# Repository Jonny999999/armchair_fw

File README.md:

# Overview
This repository contains the firmware for a custom-built automated electric armchair.  
Detailed project information and documentation is available on the website:
- ~~V1: [Electric Armchair V1](https://pfusch.zone/electric-armchair)~~
- V2: [Electric Armchair V2](https://pfusch.zone/electric-armchair-v2)

**Note:** Only the esp-project in the [board_single/](board_single) folder and the custom libraries in [common/](common) are used.  
The two-board V2.1 approach (`board_control`/`board_motorctl`) was dropped and its code removed; see tag `V2.2_new-driver` or earlier if that history is ever needed again.

<br>
*Photo of the built frame that carries the armchair*

<br>

## Current Features
- **Control Modes:**
  - **Joystick:** Control movement via hardware joystick mounted on the right armrest
  - **HTTP:** Control movement via virtual joystick on a web interface
  - **Massage:** Armchair shaking depending on stick position
  - **Adjust:** Control leg and backrest position via joystick
  - **Auto:** Execute stored driving commands sequentially
- **Advanced Motor Control:**
  - Deceleration limit
  - Acceleration limit
  - Current limit
  - Braking
  - Compatible with different motor drivers:
    - 3 pins: A, B, PWM - e.g. various common H-Bridges
    - 1 pin: UART/RS232 - e.g. Sabertooth
- **Input/Sensors:**
  - **Speed Measurement:** Measures speed and direction of each tire individually using custom built encoders
  - **Current Measurement:** Monitors current of each motor
  - **Battery Voltage:** Measures battery voltage and calculates percentage according to discharge curve
  - **Analog Joystick:** 
    - Evaluate two analog signals to get coordinates, radius and angle
    - Calibration wizard/sequence
    - Calibration stored persistently in nvs
- **Fan Control:** Cooling fan for motor driver are activated when needed only
- **Buzzer:** Provides acoustic feedback when switching modes or interacting with menu
- **OLED-Display + Rotary-encoder:**
  - Various status screens showing battery status, speed, RPM, motor current, mode, power, duty cycle, stick data
  - Menu for setting various options using encoder
  - Changed settings are stored persistently in NVS flash
  - Menu for selecting the control mode
- **UART Communication between 2 Boards (V2.1)**
- **Electric Chair Adjustment:** Control 4 Relays powering motors that adjust the chair rest positions
- **Wi-Fi:**
  - Hosts wireless network
  - Web server with webroot in SPIFFS
  - HTTP API for controlling the chair (remote control)
  - Captive portal + mDNS (`armchair.local`): the web-app opens automatically after connecting
- **React web-app:** (placed in SPIFFS)
  - *Drive* tab: virtual joystick + slider for the speed limit (max duty)
  - *Chair* tab: controls for the leg- and back-rest (hold-buttons, position slider, live position)

## Planned Features
#### Hardware
- More Sensors:
  - Accelerometer
  - Lidar sensor / collision detection
  - GPS receiver
  - Temperature sensors
- Lights
- Camera
#### Algorithms
- Anti-Slip Regulation
- Self-Driving Algorithm
#### UI
- Improved Web Interface
  - Settings
- Simple App

<br>

## Hardware Setup / Electrical
### Control-PCB
The firmware is designed for an ESP32 microcontroller integrated into a custom PCB developed here: [Project Work 2020](https://pfusch.zone/project-work-2020)

### Connection Plan
A detailed diagram illustrating all components and wiring can be found in the file [connection-plan.drawio.pdf](connection-plan.drawio.pdf).   
For more details refer to the documentation on the [website](https://pfusch.zone/electric-armchair-v2).

### Chair-Adjust Relay-Board
A custom pcb with relays and protection for controlling the 2 motors that adjust the rest positions of the armchair was created in this repository as well:
Date: 2024.09.08  
Folder: [hardware/chairAdjust-relayBoard](hardware/chairAdjust-relayBoard)  
Schematic: [hardware/chairAdjust-relayBoard/export/schematic.pdf](hardware/chairAdjust-relayBoard/export/schematic.pdf)
<br>
<br>

<br>
<br>

# Installation
### Install ESP-IDF
For this project **ESP-IDF v4.4.4** is required
```bash
#download esp-idf
yay -S esp-idf #alternatively clone the esp-idf repository from github
#run installation script in installed folder
/opt/esp-idf/install.sh
```
### Clone Repository
```
git clone git@github.com:Jonny999999/armchair_fw
```
### Install Node Packages
Navigate to the react-app directory and install required packages using npm:
```
cd react-app
npm install
```

<br>
<br>

# Building the Project
## React-webapp
When flashing to the ESP32, the files in the `react-app/build/` folder are written to a SPIFFS partition.  
These files are then served via HTTP in the Wi-Fi network "armchair" created by the ESP32.  

Initially, or when changing the React code, you need to manually build the React app:
```bash
cd react-app
npm run build
```
Note: the build script also deletes the generated `*.LICENSE.txt` (its filename is too long for spiffs).

**Testing locally:** `npm start` serves the app on the pc. To let it talk to the actual
armchair (connected to wifi `armchair`, HTTP mode) set the api host:
```bash
REACT_APP_API_HOST=http://192.168.4.1 npm start
```
**Tests:** `npm test` runs a few smoke-tests of the web-app (rendering, heartbeat, rest-buttons)

## Firmware
### Environment Setup
```bash
source /opt/esp-idf/export.sh
```
Run once per terminal

### Compilation
```bash
cd board_single
idf.py build
```

### Upload
- Connect FTDI programmer to board (GND to GND, TX to RX, RX to TX)
- Press RESET and BOOT button
- Release RESET button (keep pressing boot)
- Release boot button
- Run flash command:
```bash
idf.py flash
```

### Monitor
To view log output for debugging, follow the same steps as in the Upload section, but run:
```bash
idf.py monitor
```

<br>
<br>

# Usage / User Interface

## Quickstart
- **Browse / select any mode**
  - `[long press]` opens menu for selecting the desired mode (*JOYSTICK* for driving)
- **Driving**
  - `[3x click]` enters *JOYSTICK* mode
- **Rest position**
  - `[rotate]` adjusts the leg rest position  
  - `[press + rotate]` at the same time: adjusts the back rest position
  - alternatively enter *ADJUST* mode and control rests via joystick

<br>

## Encoder Functions
- *When not in MENU mode*, **rotating the encoder** has the following functions:

|     Encoder Event   |          Action           |
|---------------------|---------------------------|
| rotate left         | Move leg rest up by 10%   |
| rotate right        | Move leg rest DOWN by 10% |
| press + rotate left | Move back rest down by 5% |
| press + rotate left | Move back rest up by 5%   |

Note: first tick is ignored -> quickly rotate 2 ticks at first

<br>

- *When not in MENU mode*, **clicking the encoder** has the following functions:

| Count | Type          | Action               | Description                                                                                 |
|-------|---------------|----------------------|---------------------------------------------------------------------------------------------|
| 1x long | switch mode | **MENU_MODE_SELECT** | Open **menu for selecting the current control mode**                                            |
| 1x      | control     | [MASSAGE] **freeze** input  | When in massage mode: lock or unlock joystick input at current position.             |
| 1x short, 1x long | switch mode | **ADJUST-CHAIR**  | Switch to mode where the armchair leg and backrest are controlled via joystick.      |
| 2x      | toggle mode | **IDLE** <=> previous| Enable/disable chair armchair (e.g., enable after startup or switch to previous mode after timeout). |
| 3x      | switch mode | **JOYSTICK**         | Switch to JOYSTICK mode, to control armchair using joystick (default).                      |
| 4x      | switch mode | **HTTP**             | Switch to **remote control** via web-app `http://191.168.4.1` in wifi `armchair`.           |
| 5x      | switch mode | **MENU_SETTINGS**    | Open menu to set various options, controlled via display and rotary encoder.                |
| 6x      | switch mode | **MASSAGE**          | Switch to MASSAGE mode where armchair shakes differently, depending on joystick position.   |
| 7x      |             |                      |                                                                                             |
| 8x      | toggle option| **deceleration limit** | Disable/enable deceleration limit (default on) => more responsive.                       |
| 12x     | toggle option| **alt stick mapping** | Toggle between default and alternative stick mapping (reverse direction swapped).         |

<br>

- When in **MENU_SETTINGS mode** (5x click), the encoder controls the settings menu: (similar in MENU_MODE_SELECT)

| Encoder Event | Current Menu | Action                                                       |
|---------------|--------------|--------------------------------------------------------------|
| long press    | main-menu    | Exit MENU mode to previous control mode (e.g., JOYSTICK).    |
| long press    | value-select | Exit to main-menu without changing the value.                |
| click         | main-menu    | Select currently highlighted menu item -> enter value-select screen. |
| click         | value-select | Confirm value / run action.                                  |
| rotate        | main-menu    | Scroll through menu items.                                   |
| rotate        | value-select | Change value.                                                |

<br>

## HTTP Mode
Control the armchair via a virtual joystick on the web interface.

**Usage:**
- Switch to HTTP mode (4 button presses or via mode-select menu).
- Connect to WiFi `armchair`, no password.
- A sign-in page should open **automatically**:
  - *iOS:* the "sign in to network" window pops up on its own
  - *Android / Windows:* a notification "Sign in to Wi-Fi network" appears, tap it
- That page shows the address to copy into the browser (long-press or the copy button).
  It is only a sign-in window, not a real browser - the joystick misbehaves in it (see below).
- If it does not open automatically, any of these work:
  - open http://armchair.local
  - open http://192.168.4.1
  - simply enter **any** address (e.g. `http://a`) - all hostnames resolve to the armchair

Note: use **http**, NOT https - some browsers automatically add https, which does not work.

**Features of the web-app:**

The app has two tabs, so nothing except the joystick is tappable while driving blindly.

- ***Drive* tab:** virtual joystick + speed limit
  - The controller stops the motors when it receives no data for 2.5s (safety, e.g. lost
    connection). Coordinates are sent on joystick events *and* repeated once per second as
    heartbeat, so holding the stick still while driving straight does not stop the chair.
  - The **speed limit** slider changes the same *max duty* setting as the encoder-menu.
    It sits at the top, far away from the joystick at the bottom, and is only sent when
    the slider is *released* (the controller stores the value in NVS flash).
  - Leaving the tab sends a final "center" - the chair stops instead of waiting for the timeout.
  - Below the joystick: battery percentage/voltage and the power the two motors are currently
    drawing. Not tappable and of a fixed height, so it can not interfere with driving.
- ***Chair* tab:** leg- and back-rest
  - hold the direction buttons to move the rest as long as they are pressed
  - Note: for the back-rest `0%` is *upright* and `100%` is reclined, so its buttons are
    labelled `flatten`/`upright` instead of up/down (which would be the wrong way round)
  - slider / presets to move to a certain position
  - the position tracked by the controller is shown live (also updates when the rest is
    moved with the encoder)
  - Note: sending `0%`/`100%` while already at that position is not ignored - the motor runs
    into the limit switch again, which re-syncs the (time based) position tracking

**How it works:** while in HTTP mode the ESP32 runs a captive portal - a DNS server
answering every query with its own IP ([common/dns_server.c](common/dns_server.c)) plus an
HTTP redirect for all foreign hosts ([common/http.cpp](common/http.cpp)). That is exactly what
phones use to detect "this network requires sign in", which makes them offer/open the
sign-in page on their own. Additionally mDNS provides the hostname `armchair.local`.

The window the phone opens it in is *not* the browser of the user but a stripped down webview
("captive network assistant"), which e.g. fires its pull-to-refresh while dragging the
joystick downwards and does not let the page disable it. A page can not open the real browser
either - `target="_blank"` and `intent://` urls are both blocked there. So that window only
gets a small landing page handing out the address to copy over manually.

The sign-in is never confirmed automatically: confirming it closes that window, and while it
is unconfirmed the page stays reachable through the notification. The "confirm sign-in" link
at the bottom of it does so manually (`/portal/done`) - from then on the connectivity-probes
are answered like a working internet connection (`204` / `Success`) and the phone stops
nagging. It is armed again whenever a station joins the access-point.

Note that only the well-known probe URLs are answered that way; browsing to any other
address (e.g. `google.com`) keeps redirecting to the web-app the whole time.

**HTTP-API** (see [common/http.cpp](common/http.cpp)):

| Method | Endpoint        | Payload / Response                                                        |
|--------|-----------------|---------------------------------------------------------------------------|
| POST   | `/api/joystick` | `{"x":0.5,"y":-0.2}` - coordinates -1 to 1                                |
| POST   | `/api/chair`    | `{"rest":"leg"\|"back", "action":"up"\|"down"\|"stop"}` - move while held |
| POST   | `/api/chair`    | `{"rest":"leg"\|"back", "percent":0-100}` - move to position              |
| GET    | `/api/chair`    | `{"leg":{"percent":..,"target":..,"state":".."},"back":{...}}`            |
| POST   | `/api/settings` | `{"maxDuty":65}` - top speed limit 1-100 (stored in nvs)                   |
| GET    | `/api/settings` | `{"maxDuty":65}`                                                          |
| GET    | `/api/status`   | battery percent/voltage + current, power and duty of both motors          |

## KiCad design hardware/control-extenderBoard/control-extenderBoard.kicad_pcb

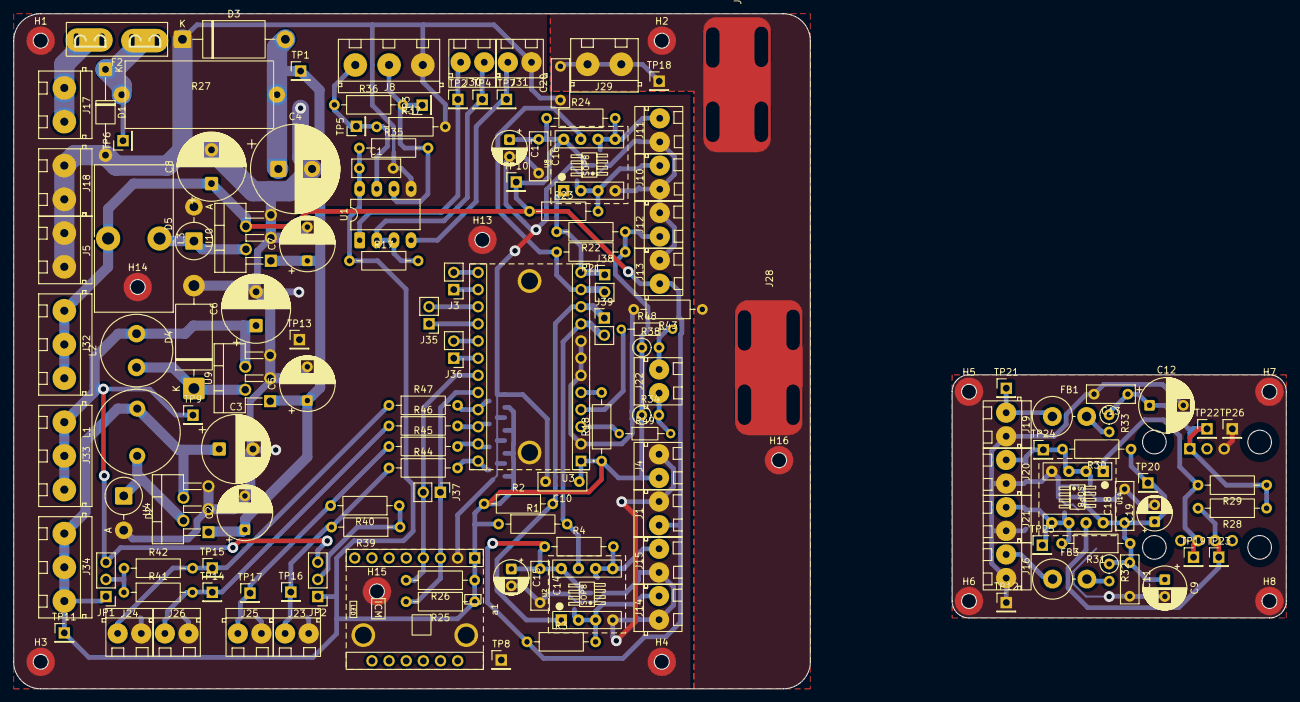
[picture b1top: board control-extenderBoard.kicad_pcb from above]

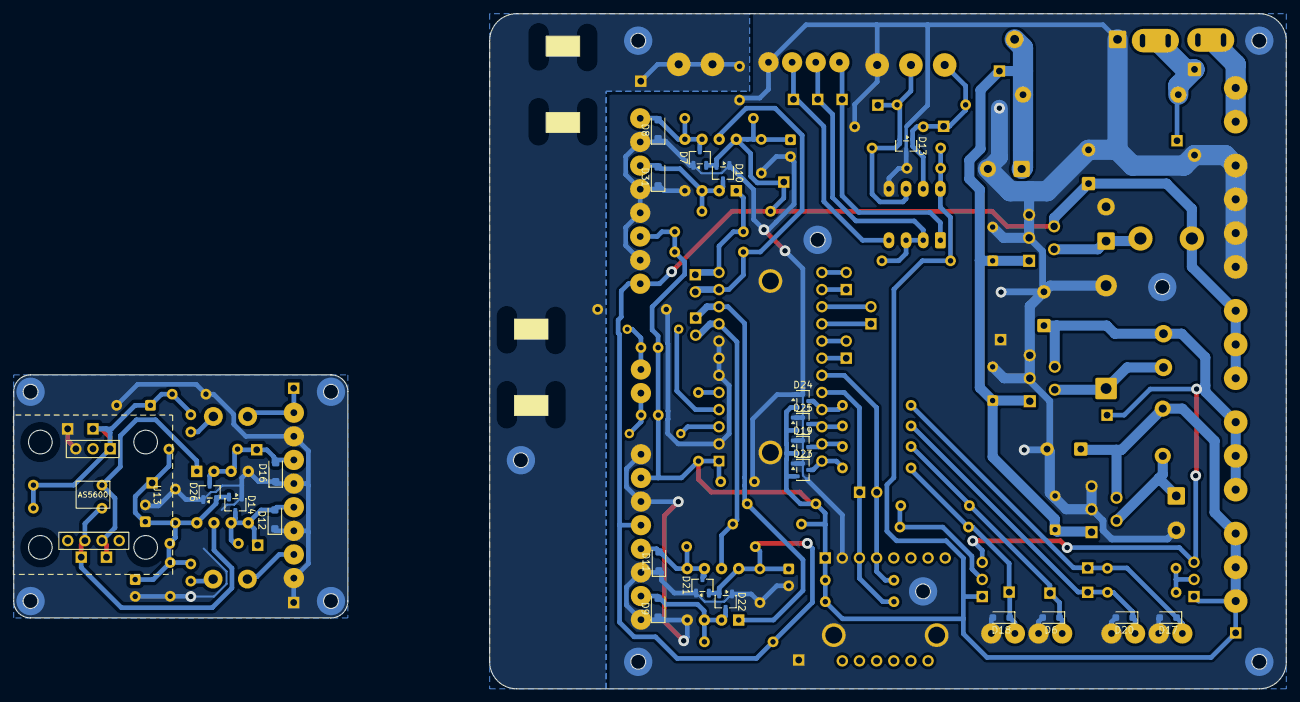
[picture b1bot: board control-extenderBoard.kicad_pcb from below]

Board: 4 copper layers, 188.5 x 100.0 mm, 172 parts (22 on the bottom side), 58 nets.

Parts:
C1, C10, C11, C13, C14, C16, C18, C20: 100n; C_Disc_D7.0mm_W2.5mm_P5.00mm
C2, C5, C7, C12: 100u; CP_Radial_D8.0mm_P5.00mm
C3, C6, C8: 1000u; CP_Radial_D10.0mm_P5.00mm
C4: 2200uf; CP_Radial_D13.0mm_P5.00mm
C9: 100u; CP_Radial_D6.3mm_P2.50mm
C15, C17, C19: 10uf; CP_Radial_D5.0mm_P2.50mm
D1: D; D_T-1_P12.70mm_Horizontal
D2, D5: 1N5822; D_DO-201AE_P5.08mm_Vertical_AnodeUp
D3: TVS 28V (starts 31V); D_DO-201AE_P15.24mm_Horizontal
D4: 1N5822; D_DO-201AD_P15.24mm_Horizontal
D6, D17, D18, D20: AQ4020-01FTG; D_SOD-323_HandSoldering
D7, D10, D14, D19, D21, D22, D23, D24, D25, D26: BAS70-04; SOT-23-3
D8, D9, D11, D12, D16, D31: PESD12VL1BA; D_SOD-123F
D13: SM712_SOT23; SOT-23
F2: F-total-control-supply; Fuseholder_Automotive-Mini_Fuse11x4x16_Footprint15x5_Inline
FB1, FB3: FerriteBead AWBC-09; R_Axial_DIN0614_L14.3mm_D5.7mm_P5.08mm_Vertical
H1, H2, H3, H4, H5, H6, H7, H8, H13, H14, H15, H16: MountingHole_Pad; MountingHole_2.2mm_NPTH-with-pad_DRC-clearance-error
J1, J13, J16: 12V + GND (TP); ScrewTerminal_P3.5mm_2Pin_FP7x7
J3, J35, J36, J37, J38, J39: Conn_01x02_Pin; PinHeader_1x02_P2.54mm_Vertical
J4, J12, J19: 3V3 + GND (TP); ScrewTerminal_P3.5mm_2Pin_FP7x7
J5, J18: GND; ScrewTerminal_P5mm_2Pin_FP10x8
J8: RS485; ScrewTerminal_P5mm_3Pin_FP15x8
J10: SCL1 + GND (TP); ScrewTerminal_P3.5mm_2Pin_FP7x7
J11: SDA1 + GND (TP); ScrewTerminal_P3.5mm_2Pin_FP7x7
J14: SCL0 + GND (TP); ScrewTerminal_P3.5mm_2Pin_FP7x7
J15: SDA0 + GND (TP); ScrewTerminal_P3.5mm_2Pin_FP7x7
J17: 24V IN; ScrewTerminal_P5mm_2Pin_FP10x8
J20: SCL6 + GND (TP); ScrewTerminal_P3.5mm_2Pin_FP7x7
J21: SDA6 + GND (TP); ScrewTerminal_P3.5mm_2Pin_FP7x7
J22: SDA, SCL - ESP32; ScrewTerminal_P3.5mm_2Pin_FP7x7
J23: I2C7 Reserve SCL/GND; ScrewTerminal_P3.5mm_2Pin_FP7x7
J24: I2C6 Reserve SDA/GND; ScrewTerminal_P3.5mm_2Pin_FP7x7
J25: I2C7 Reserve SDA/GND; ScrewTerminal_P3.5mm_2Pin_FP7x7
J26: I2C6 Reserve SCL/GND; ScrewTerminal_P3.5mm_2Pin_FP7x7
J27, J28: CAT6-Shield; Shield_Landing_Pad_6mmCable_ZipTie
J29: Chassis; ScrewTerminal_P5mm_2Pin_FP10x8
J30: RX DIR; ScrewTerminal_P3.5mm_2Pin_FP7x7
J31: TX, GND; ScrewTerminal_P3.5mm_2Pin_FP7x7
J32: 12V out; ScrewTerminal_P5mm_3Pin_FP15x8
J33: 5V out; ScrewTerminal_P5mm_3Pin_FP15x8
J34: 3V3 out; ScrewTerminal_P5mm_3Pin_FP15x8
JP1, JP2: sel 3V vs 5V pullup; PinHeader_1x03_P2.54mm_Vertical
L1: 150u; L_Radial_D12.5mm_P7.00mm_Fastron_09HCP
L2: 330u; L_Radial_D10.5mm_P5.00mm_Abacron_AISR-01
L3: 470u; L_Toroid_Vertical_L21.6mm_W11.4mm_P7.62mm_Pulse_KM-3
R1, R2, R21, R22, R25, R26, R28, R29, R39, R40, R41, R42: 2k2; R_Axial_DIN0207_L6.3mm_D2.5mm_P10.16mm_Horizontal
R3, R4, R23, R24, R30, R31: 750; R_Axial_DIN0207_L6.3mm_D2.5mm_P10.16mm_Horizontal
R17, R18: 10k; R_Axial_DIN0207_L6.3mm_D2.5mm_P10.16mm_Horizontal
R27: 2.5; Cement-Power-R_L22_W10_P23_Horizontal
R32, R33: 10; R_Axial_DIN0207_L6.3mm_D2.5mm_P2.54mm_Vertical
R34, R38: 2k2; R_Axial_DIN0207_L6.3mm_D2.5mm_P2.54mm_Vertical
R35, R37: 470; R_Axial_DIN0207_L6.3mm_D2.5mm_P10.16mm_Horizontal
R36: 120; R_Axial_DIN0207_L6.3mm_D2.5mm_P10.16mm_Horizontal
R43: 1M; R_Axial_DIN0207_L6.3mm_D2.5mm_P10.16mm_Horizontal
R44, R45, R46, R47: 22; R_Axial_DIN0207_L6.3mm_D2.5mm_P10.16mm_Horizontal
R48, R49: 22; R_Axial_DIN0204_L3.6mm_D1.6mm_P7.62mm_Horizontal
TP1: 24V filtered; PinHeader_1x01_P2.54mm_Vertical
TP2: RX; PinHeader_1x01_P2.54mm_Vertical
TP3: TP A; PinHeader_1x01_P2.54mm_Vertical
TP4: DE; PinHeader_1x01_P2.54mm_Vertical
TP5: TP B; PinHeader_1x01_P2.54mm_Vertical
TP6: BATT; PinHeader_1x01_P2.54mm_Vertical
TP7: TX; PinHeader_1x01_P2.54mm_Vertical
TP8, TP12, TP13, TP26: GND; PinHeader_1x01_P2.54mm_Vertical
TP9: 5V; PinHeader_1x01_P2.54mm_Vertical
TP10: 12V; PinHeader_1x01_P2.54mm_Vertical
TP11: 3V3; PinHeader_1x01_P2.54mm_Vertical
TP14: SCL6; PinHeader_1x01_P2.54mm_Vertical
TP15: SDA6; PinHeader_1x01_P2.54mm_Vertical
TP16: SCL7; PinHeader_1x01_P2.54mm_Vertical
TP17: SDA7; PinHeader_1x01_P2.54mm_Vertical
TP18: Chassis; PinHeader_1x01_P2.54mm_Vertical
TP19: SCL; PinHeader_1x01_P2.54mm_Vertical
TP20: 12V-Filtered; PinHeader_1x01_P2.54mm_Vertical
TP21: 3V3-IN; PinHeader_1x01_P2.54mm_Vertical
TP22: 3V3-Filtered; PinHeader_1x01_P2.54mm_Vertical
TP23: SDA; PinHeader_1x01_P2.54mm_Vertical
TP24: SCL-in; PinHeader_1x01_P2.54mm_Vertical
TP25: SDA-in; PinHeader_1x01_P2.54mm_Vertical
U1: MAX3485; DIP-8_W7.62mm_LongPads
U2, U8, U14: PCA9600D; Adapter-Board_SOP8_to_DIP8
U3: TCA9548A_1-to-8_I2C_Multiplexer_Breakout-Board; TCA9548A_1-to-8_I2C_Multiplexer_Breakout_Board
U4: LM2576T-3.3; TO-220-5_P3.4x3.7mm_StaggerOdd_Lead3.8mm_Vertical
U9: LM2576T-5; TO-220-5_P3.4x3.7mm_StaggerOdd_Lead3.8mm_Vertical
U10: LM2576T-12; TO-220-5_P3.4x3.7mm_StaggerOdd_Lead3.8mm_Vertical
U13: AS5600_Breakout; AS5600_Magnetic-Encoder_Breakout_Board
a1: ICM-426XX_Breakout; ICM-426XX_6-Axis-Gyro_Breakout_Board

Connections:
+3V3: C1.1, C3.1, C10.1, D19.2 (K), D23.2 (K), D24.2 (K), D25.2 (K), J4.1, J12.1, J34.1, J34.2, J34.3, JP1.1 (A), JP2.1 (A), L1.2, R1.1, R2.1, R17.1, R18.1, R21.1, R22.1, R25.1, R26.1, R34.1, R35.1, R38.1, TP11.1, U1.8 (VCC), U3.1 (VIN), U4.4 (FB), a1.1 (VCC)
+3V3_REMOTE: C12.1, C13.1, R28.1, R29.1, R33.1, TP22.1, U13.1 (VCC)
+5V: C6.1, J33.1, J33.2, J33.3, JP1.3 (B), JP2.3 (B), L2.2, TP9.1, U9.4 (FB)
+12V: C8.1, C14.1, C15.1, C16.1, C17.1, D7.2 (K), D10.2 (K), D21.2 (K), D22.2 (K), J1.1, J13.1, J32.1, J32.2, J32.3, L3.2, R3.1, R4.1, R23.1, R24.1, TP10.1, U2.8 (VCC), U8.8 (VCC), U10.4 (FB)
+12V_REMOTE: C9.1, C11.1, C18.1, C19.1, D14.2 (K), D26.2 (K), R30.1, R31.1, R32.1, TP20.1, U14.8 (VCC)
+24V filtered: C2.1, C4.1, C5.1, C7.1, D3.2 (A2), R27.2, TP1.1, U4.1 (VIN), U9.1 (VIN), U10.1 (VIN)
+BATT: F2.2, J17.1, J17.2
/ESP32_SCL: J22.2, R38.2, R48.2
/ESP32_SDA: J22.1, R34.2, R49.2
/I2C0_SCL: J39.1, R2.2, U2.1 (SX), U3.10 (SCL0)
/I2C0_SDA: J39.2, R1.2, U2.7 (SY), U3.9 (SDA0)
/I2C1_SCL: J38.1, R22.2, U3.12 (SCL1), U8.1 (SX)
/I2C1_SDA: J38.2, R21.2, U3.11 (SDA1), U8.7 (SY)
/I2C2_SCL: J3.1, U3.14 (SCL2)
/I2C2_SDA: J3.2, U3.13 (SDA2)
/I2C3_SCL: J35.1, U3.16 (SCL3)
/I2C3_SDA: J35.2, U3.15 (SDA3)
/I2C4_SCL: J36.1, U3.18 (SCL4)
/I2C4_SDA: J36.2, U3.17 (SDA4)
/I2C5_SCL: J37.1, R25.2, U3.20 (SCL5), a1.3 (SCL)
/I2C5_SDA: J37.2, R26.2, U3.19 (SDA5), a1.4 (SDA)
/I2C6_SCL: D25.3 (COM), R46.2, U3.22 (SCL6)
/I2C6_SDA: D24.3 (COM), R47.2, U3.21 (SDA6)
/I2C7_SCL: D23.3 (COM), R44.2, U3.24 (SCL7)
/I2C7_SDA: D19.3 (COM), R45.2, U3.23 (SDA7)
/MASTER_SCL: R48.1, U3.4 (SCL)
/MASTER_SDA: R49.1, U3.3 (SDA)
/RS485-A: D13.2 (A2), J8.2, R35.2, R36.2, TP3.1, U1.6 (A)
/RS485-B: D13.1 (A1), J8.3, R36.1, R37.1, TP5.1, U1.7 (B)
/RS485_DIR: J30.1, R17.2, TP4.1, U1.2 (~RE), U1.3 (DE)
/RS485_RX: J30.2, TP2.1, U1.1 (RO)
/RS485_TX: J31.2, TP7.1, U1.4 (DI)
/Remote-I2C-Sensor-Board/3V3_REMOTE-IN: FB1.1, J19.1, TP21.1
/Remote-I2C-Sensor-Board/12V_REMOTE-IN: FB3.1, J16.1
/Remote-I2C-Sensor-Board/SCL_AS5600: R29.2, TP19.1, U13.6 (SCL), U14.1 (SX)
/Remote-I2C-Sensor-Board/SCL_REMOTE-IN: D16.2 (A2), D26.3 (COM), J20.1, R30.2, TP24.1, U14.2 (RX), U14.3 (TX)
/Remote-I2C-Sensor-Board/SDA_AS5600: R28.2, TP23.1, U13.5 (SDA), U14.7 (SY)
/Remote-I2C-Sensor-Board/SDA_REMOTE-IN: D12.2 (A2), D14.3 (COM), J21.1, R31.2, TP25.1, U14.5 (TY), U14.6 (RY)
/SCL0_Boost: D9.2 (A2), D22.3 (COM), J14.2, R3.2, U2.2 (RX), U2.3 (TX)
/SCL1_Boost: D10.3 (COM), D31.2 (A2), J10.2, R23.2, U8.2 (RX), U8.3 (TX)
/SDA0_Boost: D11.2 (A2), D21.3 (COM), J15.2, R4.2, U2.5 (TY), U2.6 (RY)
/SDA1_Boost: D7.3 (COM), D8.2 (A2), J11.2, R24.2, U8.5 (TY), U8.6 (RY)
Chassis: C20.2, H2.1, H16.1, J27.1, J28.1, J29.1, J29.2, R43.1, TP18.1
GND: C1.2, C2.2, C3.2, C4.2, C5.2, C6.2, C7.2, C8.2, C10.2, C14.2, C15.2, C16.2, C17.2, C20.1, D1.2 (A), D2.2 (A), D3.1 (A1), D4.2 (A), D5.2 (A), D6.2 (A2), D7.1 (A), D8.1 (A1), D9.1 (A1), D10.1 (A), D11.1 (A1), D13.3 (common), D17.2 (A2), D18.2 (A2), D19.1 (A), D20.2 (A2), D21.1 (A), D22.1 (A), D23.1 (A), D24.1 (A), D25.1 (A), D31.1 (A1), H1.1, H3.1, H4.1, H13.1, H14.1, H15.1, J1.2, J4.2, J5.1, J5.2, J8.1, J10.1, J11.1, J12.2, J13.2, J14.1, J15.1, J18.1, J18.2, J23.2, J24.2, J25.2, J26.2, J31.1, R37.2, R43.2, TP8.1, TP13.1, U1.5 (GND), U2.4 (GND), U3.2 (GND), U3.6 (A0), U3.7 (A1), U3.8 (A2), U4.3 (GND), U4.5 (~ON/OFF), U8.4 (GND), U9.3 (GND), U9.5 (~ON/OFF), U10.3 (GND), U10.5 (~ON/OFF), a1.2 (GND)
GND_REMOTE: C9.2, C11.2, C12.2, C13.2, C18.2, C19.2, D12.1 (A1), D14.1 (A), D16.1 (A1), D26.1 (A), H5.1, H6.1, H7.1, H8.1, J16.2, J19.2, J20.2, J21.2, TP12.1, TP26.1, U13.3 (GND), U14.4 (GND)
unnamed: D1.1 (K), F2.1, R27.1, TP6.1
unnamed: D2.1 (K), L1.1, U4.2 (OUT)
unnamed: D4.1 (K), L2.1, U9.2 (OUT)
unnamed: D5.1 (K), L3.1, U10.2 (OUT)
unnamed: D6.1 (A1), J25.1, R40.2, R45.1, TP17.1
unnamed: D17.1 (A1), J24.1, R42.2, R47.1, TP15.1
unnamed: D18.1 (A1), J23.1, R39.2, R44.1, TP16.1
unnamed: D20.1 (A1), J26.1, R41.2, R46.1, TP14.1
unnamed: FB1.2, R33.2
unnamed: FB3.2, R32.2
unnamed: JP1.2 (C), R41.1, R42.1
unnamed: JP2.2 (C), R39.1, R40.1
unnamed: R18.2, U3.5 (RST)

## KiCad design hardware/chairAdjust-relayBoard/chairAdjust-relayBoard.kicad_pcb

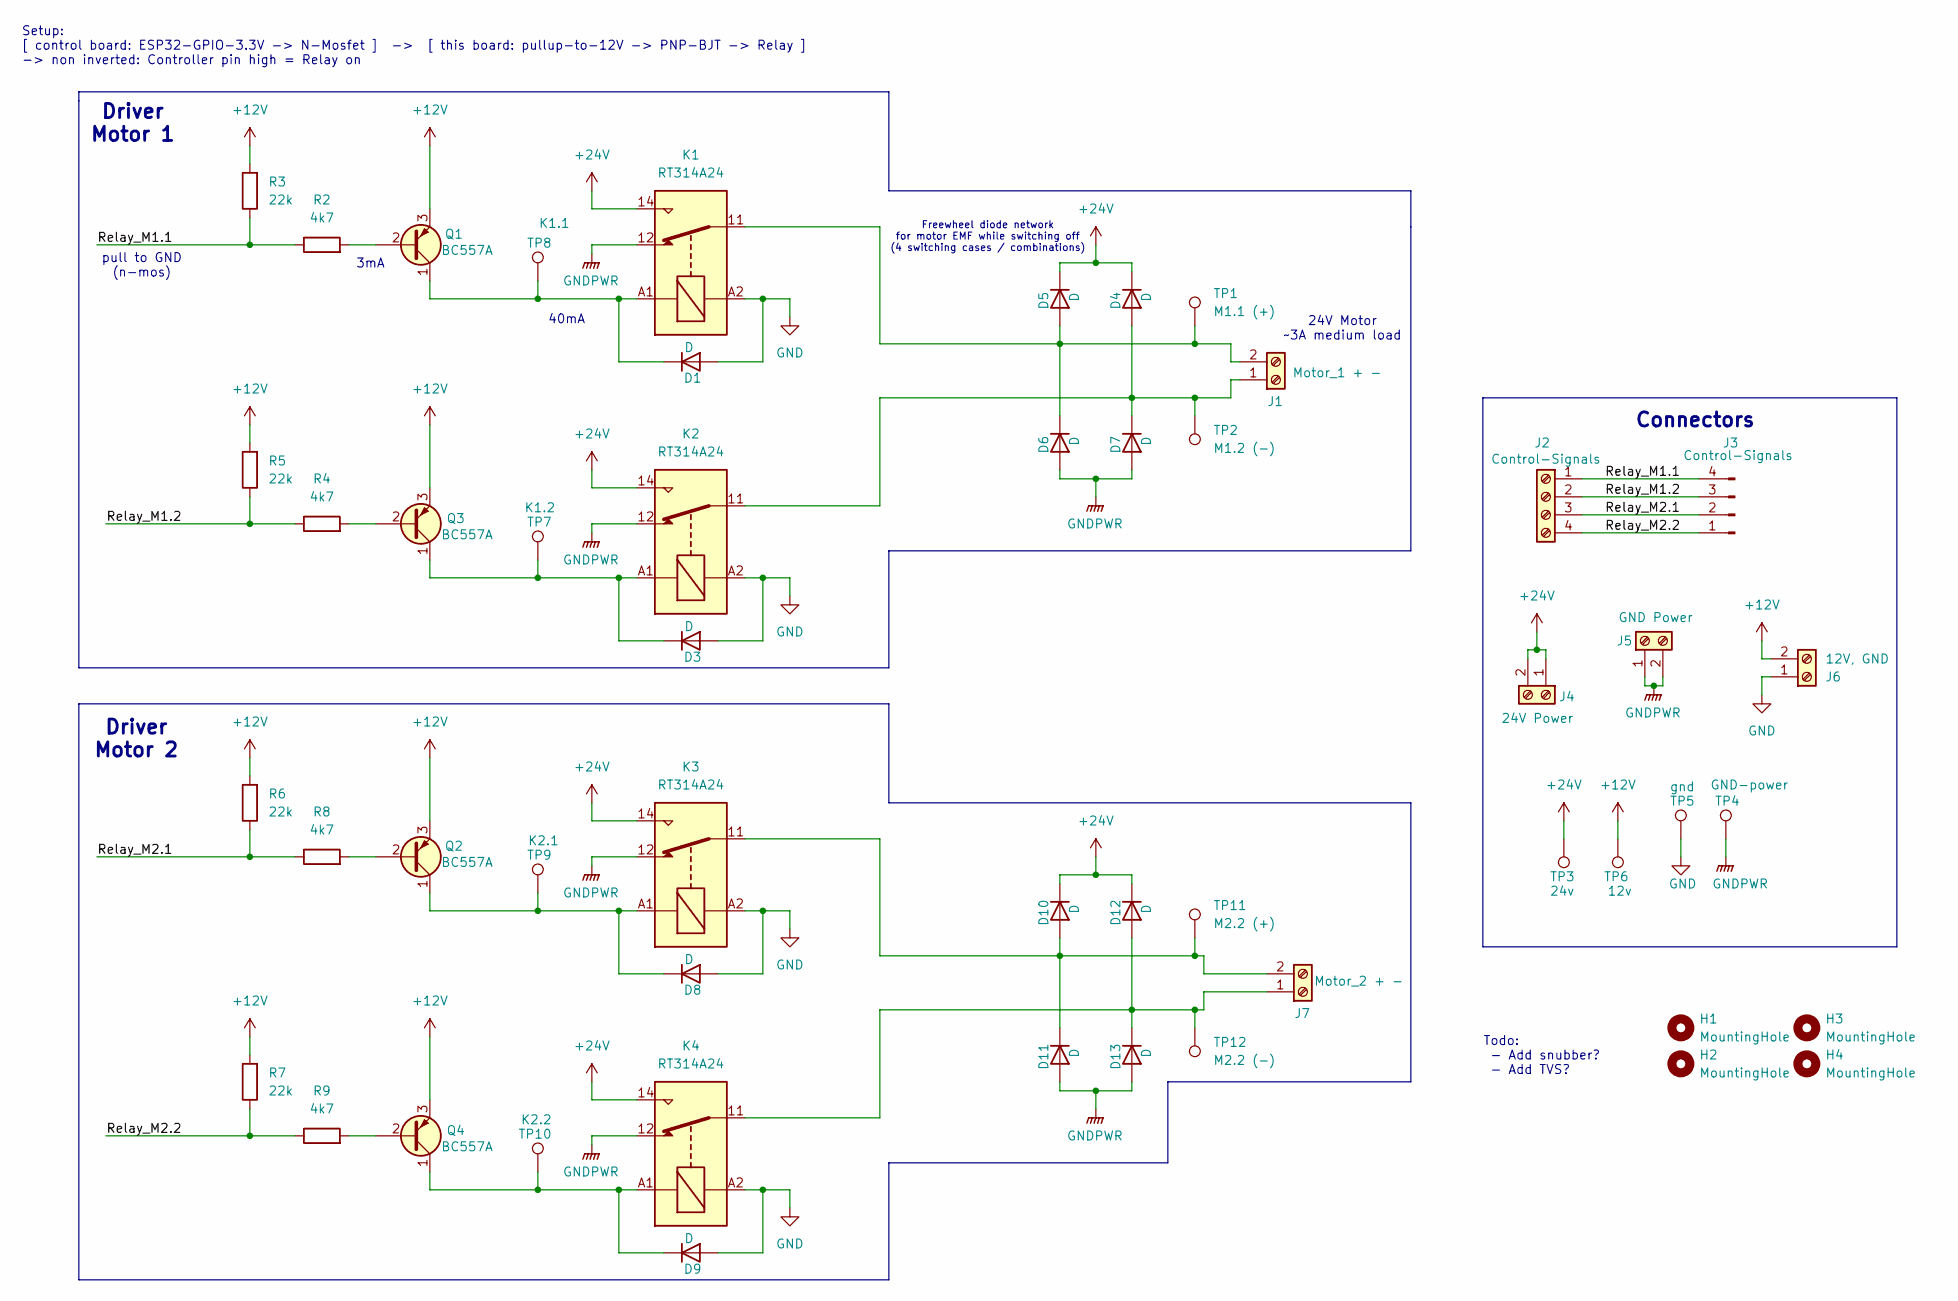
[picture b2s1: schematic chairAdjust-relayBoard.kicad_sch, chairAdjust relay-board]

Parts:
D1, D3, D8, D9: D; D_5W_P12.70mm_Horizontal
D4, D5, D6, D7, D10, D11, D12, D13: D; D_DO-27_P20.32mm_Horizontal
H1, H2, H3, H4: MountingHole; MountingHole_5.3mm_M5
J1: Motor_1 + -; TerminalBlock_bornier-2_P5.08mm
J2: Control-Signals; TerminalBlock_4Ucon_1x04_P3.50mm_Horizontal
J3: Control-Signals; PinHeader_1x04_P2.54mm_Vertical
J4: 24V Power; TerminalBlock_bornier-2_P5.08mm
J5: GND Power; TerminalBlock_bornier-2_P5.08mm
J6: 12V, GND; TerminalBlock_bornier-2_P5.08mm
J7: Motor_2 + -; TerminalBlock_bornier-2_P5.08mm
K1, K2, K3, K4: RT314A24; Relay_SPDT_Schrack-RT1-16A-FormC_RM5mm
Q1, Q2, Q3, Q4: BC557A; TO-92_Inline_Wide_CBE
R2, R4, R8, R9: 4k7; R_Axial_DIN0207_L6.3mm_D2.5mm_P10.16mm_Horizontal
R3, R5, R6, R7: 22k; R_Axial_DIN0207_L6.3mm_D2.5mm_P10.16mm_Horizontal
TP1: M1.1 (+); PinHeader_1x01_P1.00mm_Vertical
TP2: M1.2 (-); PinHeader_1x01_P1.00mm_Vertical
TP3: 24v; PinHeader_1x01_P1.00mm_Vertical
TP4: GND-power; PinHeader_1x01_P1.00mm_Vertical
TP5: gnd; PinHeader_1x01_P1.00mm_Vertical
TP6: 12v; PinHeader_1x01_P1.00mm_Vertical
TP7: K1.2; PinHeader_1x01_P1.00mm_Vertical
TP8: K1.1; PinHeader_1x01_P1.00mm_Vertical
TP9: K2.1; PinHeader_1x01_P1.00mm_Vertical
TP10: K2.2; PinHeader_1x01_P1.00mm_Vertical
TP11: M2.2 (+); PinHeader_1x01_P1.00mm_Vertical
TP12: M2.2 (-); PinHeader_1x01_P1.00mm_Vertical

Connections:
+12V: J6.2, Q1.3 (E), Q2.3 (E), Q3.3 (E), Q4.3 (E), R3.2, R5.2, R6.2, R7.2, TP6.1
+24V: D4.1 (K), D5.1 (K), D10.1 (K), D12.1 (K), J4.1, J4.2, K1.14, K2.14, K3.14, K4.14, TP3.1
/Relay_M1.1: J2.1, J3.4, R2.1, R3.1
/Relay_M1.2: J2.2, J3.3, R4.1, R5.1
/Relay_M2.1: J2.3, J3.2, R6.1, R8.1
/Relay_M2.2: J2.4, J3.1, R7.1, R9.1
GND: D1.2 (A), D3.2 (A), D8.2 (A), D9.2 (A), J6.1, K1.A2, K2.A2, K3.A2, K4.A2, TP5.1
GNDPWR: D6.2 (A), D7.2 (A), D11.2 (A), D13.2 (A), J5.1, J5.2, K1.12, K2.12, K3.12, K4.12, TP4.1
unnamed: D1.1 (K), K1.A1, Q1.1 (C), TP8.1
unnamed: D3.1 (K), K2.A1, Q3.1 (C), TP7.1
unnamed: D4.2 (A), D7.1 (K), J1.1, K2.11, TP2.1
unnamed: D5.2 (A), D6.1 (K), J1.2, K1.11, TP1.1
unnamed: D8.1 (K), K3.A1, Q2.1 (C), TP9.1
unnamed: D9.1 (K), K4.A1, Q4.1 (C), TP10.1
unnamed: D10.2 (A), D11.1 (K), J7.2, K3.11, TP11.1
unnamed: D12.2 (A), D13.1 (K), J7.1, K4.11, TP12.1
unnamed: Q1.2 (B), R2.2
unnamed: Q2.2 (B), R8.2
unnamed: Q3.2 (B), R4.2
unnamed: Q4.2 (B), R9.2

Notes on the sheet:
Driver Motor 2
Connectors
Setup: [ control board: ESP32-GPIO-3.3V -> N-Mosfet ] -> [ this board: pullup-to-12V -> PNP-BJT -> Relay ] -> non inverted: Controller pin high = Relay on
24V Motor ~3A medium load
pull to GND (n-mos)
40mA
Driver Motor 1
Todo: - Add snubber? - Add TVS?
Freewheel diode network for motor EMF while switching off (4 switching cases / combinations)
3mA

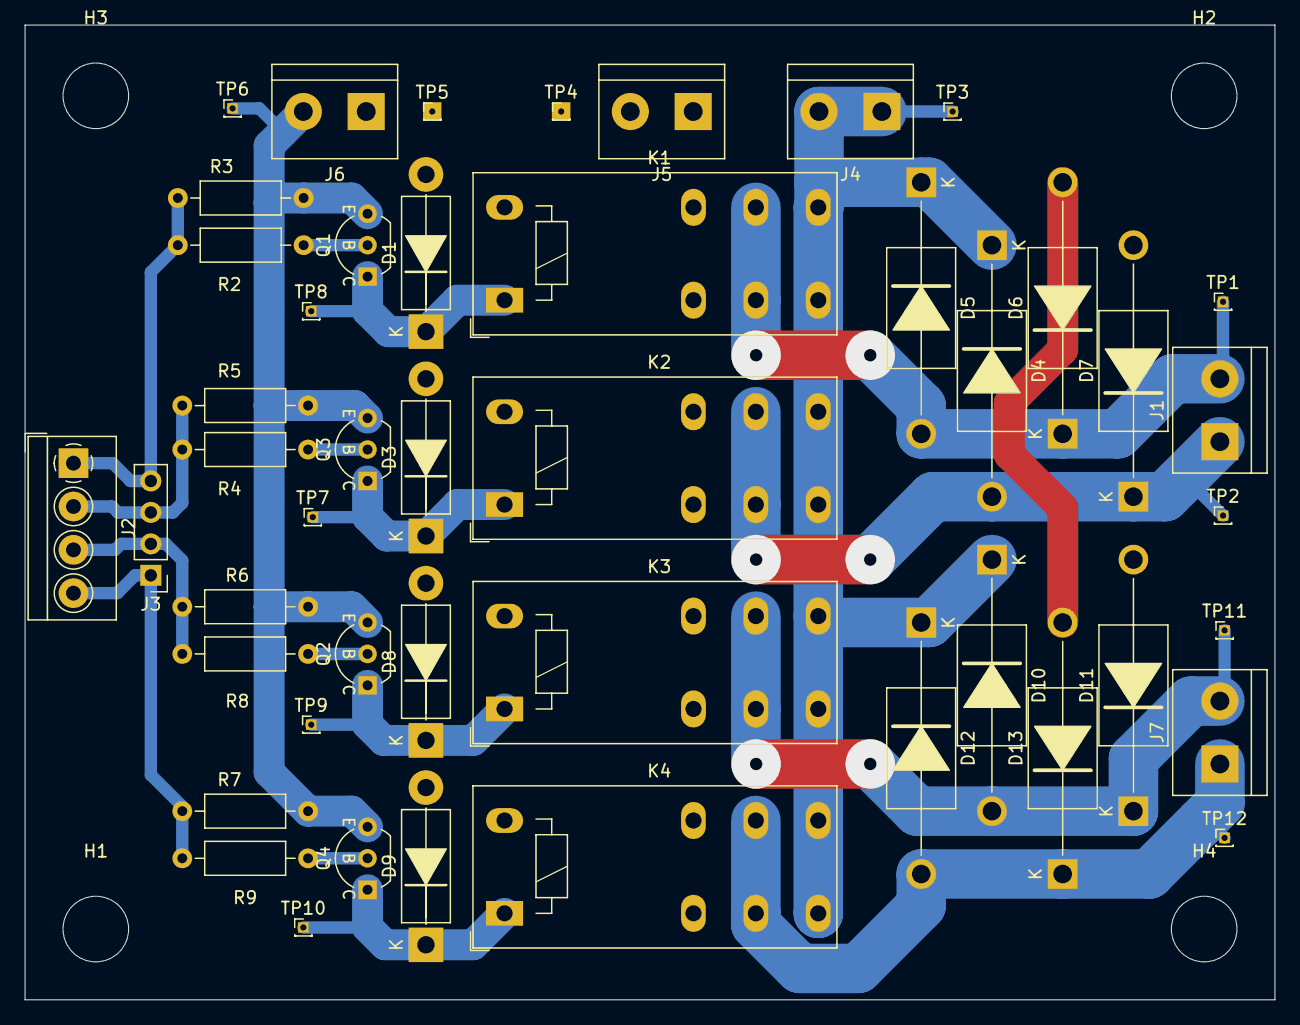
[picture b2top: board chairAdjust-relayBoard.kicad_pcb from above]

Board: 2 copper layers, 101.0 x 78.7 mm, 51 parts (0 on the bottom side), 20 nets.

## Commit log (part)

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2022-06-04 init (esp-idf sample_project)
    Rewrite of firmware controlling an electric armchair (previous firmware
    developed 2019-2021)
    - Init esp-idf project: with esp-idf version v4.4.1 installed ran command `idf.py create-project
    armchair`
    - Add connection plan from old repo
2022-06-04 Create README.md: Instructions, Documentation
    - Add brief description
    - Add installation and compilation instructions
    - Add links to websites and connection-plan
    - Add planned features
    - Add Usage section with usage description of old firmware
2022-06-09 Add 'motorRight' instance and configuration
2022-06-10 Create 'control.hpp/cpp', Create 'button.hpp/cpp'
    Add control.hpp and control.cpp
    - task that repeatedly generates motor commands depending on the current mode
    - function to change to a specified control mode
    Add button.hpp and button.cpp
    - class which runs commands depending on the count a button was pressed
    Update main.cpp
2022-06-17 Move joystick pos-definition to separate function
    Move section that defines joystick position enum to a separate function
    (outside of joystick class), this makes it usable for other inputs as
    well
    - create new function joystick_evaluatePosition
    - call the new function in joystickgetData (where code was initially)
    - change function joystick_generateCommandsDriving to accept joystick
2022-06-17 Update gitignore: Add react files
    Add files generated in the react directory that need no version control
2022-06-18 Add static ip for wifi client (10.0.0.66)
    When connecting to wifi (currently BKA-network only) a static ip
    10.0.0.66 is used.
    TODO: define static ip for access-point mode
2022-06-21 Move config parameters from control to config
    - create new struct control_config_t with several variables previously
    hardcoded in control.cpp
    - modified constructor: add config parameter
    - add definition of config struct in config.cpp
    typedef struct control_config_t {
    controlMode_t defaultMode; //default mode after startup and toggling IDLE
2022-06-25 Create shake mode (basic functionality)
    - add function joystick_generateCommandsShaking that generates motor
    commands from joystick data
    - pulses motors:
    - intervals depend on joystick radius
    - direction depends on joystick position (currently only on-x-axis and on-y-axis
    supported)
2022-07-08 Add hysteresis to joystick position X-Axis [WIP]
    modified function
    joystickPos_t joystick_evaluatePosition(float x, float y, joystickPos_t* prevPos)
    because prevPos has to be stored http.cpp/hpp and joystick.cpp/hpp had
    to be updated as well
    TODO: add function without hysteresis again?
    WIP this has to be tested
2022-07-17 Fix bug no fwd downfade; Add BRAKE; cleanup; [bug]
    - Fix bug where downfade did not work when driving forward
    - Add BRAKE command functionality to motorctl (untested, since not used anywhere atm)
    - Cleanup: Optimize code, add comments
    !!!TODO: there is a fault in the current concept/logic:
    fading up/down generally works, however when accelerating
    REVERSE fade-down is utilized instead of fade-up.
2022-07-24 Modify fading when switching from/to MASSAGE mode
    In massage mode it is required that the motors react quicker, Added the
    following functionality to control.cpp:
    - when changing to MASSAGE mode the downfading is disabled and upfading is
    reduced
    - when changing from MASSAGE mode downfading is enabled and upfading reset
    to default value
2022-07-26 Add button cmd x12: alternative joystick mapping
    New command and feature also made some general changes to control and button necessary
    joystick.cpp:
    - add optional parameter to joystick_CommandsDriving function
    bool altStickMapping (default false)
    if true this currently swaps BOTTOM_LEFT with BOTTOM_RIGHT for experimental
    different joystick mapping
2022-08-11 Fix stack overflow, apply and restore fading [functional]
    auto.cpp:
    apply fadeAccel and fadeDecel from commands to motors
    main.cpp:
    double stack size of button task (crashed controller every time)
    button.cpp:
    Modify test command to actually eject armchair leg support
2023-05-14 Update Readme: http usage, Connection-plan: add Date
    Readme
    - add todo section
    - add http usage
    Add date to connection plan
2023-08-15 Rework fan control: single pin, more delay, config
    - remove second fan instance since both fans are controlled via one pin
    now
    - more config options so fans turn on less at short movements
    => less noise and less relay cycles
2023-08-21 evaluatedSwitch: avoid random trigger (increase threshold)
    - with new hardware noticed that sometimes switch gets triggered x1
    randomly when driving forward (EMI ?)
    - increased delay options (less responsive but more controlled)
2023-08-22 Add deadTime support (time off between dir change)
    add config option for minimum time motor has to be in IDLE before
    changing direction. Try to prevent drivers from obvious extreme
    overload. At least prevent full speed switch
    Untested but simulated via log output
2023-08-30 2 boards: split code, outsource common, remove duplicate files
    - outsoruce common files and separate common types from source files (new
    common/types.hpp)
    - split source files to 2 board folders (relevant only, no duplicate)
    - currently boards compile successfull but not functional at all
    - comment out currently incompatible code
2023-08-30 Control: Rework timeout to work standalone (untested)
    rework and enable timeout feature to work independent of handledmotor
    object now uses generated commands instead of acutal motor duty
    not testet yet
2023-09-04 Update configs according to new pin assignment
    current config of each board now matches pin assignment
2023-09-05 Update function-diagram: Add UART structs
    add section where data sent with uart is planned
    also add note that diagrams are outdated
2023-09-07 Outsource currentsensor, motorctl, motordrivers to common/
    since board_single uses mostly the same code as board_control and
    board_motorctl several files are outsorced to common folder to prevent
    dupliate code and different versions
2023-09-08 Make drivers interchangeable, Switch to sabertooth driver
    - make motorctl compatible with different drivers
    - pass set function instead of specific motor object
    - add lambda function in config.cpp
    - update config to use one new sabertooth driver instead of two single100a
    - main test controlled motor
2023-09-09 Add display library, show battery voltage
    untested
2023-09-12 Outsource speedsensor, Display: show speed
    - move speedsensor files from motorctl pcb to common
    - single pcb create and configure global speedsensor objects
    - display: create fast slow veryslow loop
    - clear display every 30s
    - show speed in rpm and km/h
    NOTE: speedsensor needs fix, direction unreliable
2023-09-15 Config: Update accel and decel to tested values
2023-10-08 Add chairAdjust driver, Add joystick control
    - Add functions that control the relays for adjusting the armchair
    position
    - Add function that controls the chair using joystick input
2024-02-11 Rework/simplify chairAdjust - now using a class
    - complete rework of chairAdjust.cpp/.hpp
    created a class cControlledRest which is more readable
    and saves a lot of duplicate code
    - joystick.cpp: move chair control via joystick to
    chairAdjust.cpp (prevents dependency loop)
    - button.cpp: fix bug instant idle when changing to ADJUST_CHAIR
2024-02-14 Add functional menu items (accel/decel), Add menu-timeout
    menu.cpp:
    - add item center-Joystick (functional)
    - add item accel-Limit (functional)
    - add item decel-Limit (functional)
    - fix display freeze on timeout
    - add menu timeout
2024-02-19 Initialize motorDriver in STACK instead of HEAP, pointer
    Since moving all objects to heap encoder started to lag
    interrupt not recognizing some single events in MENU
    fast executen of motordriver setTarget caused the lag,
    initialize it in STACK while still using a pointer now
2024-02-20 Fix Motor jump at startup / always on - all modes tested
    While testing the new commits on actual hardware noticed
    the motors always beeing on at full power.
    -> This was due to uninitialized value. It had to fade down from
    duty 81236182734612738 which takes forever.
    -> This also fixes the old issue where left motor jumped for a
    second after startup
2024-02-20 Add default-value to Menu, Optimize value-screen, Add Beeping
    menu:
    - optimize set-value page: send static content only once
    so only update value -> significant performance boost
    - formatting
    - reset control timeout to prevent unintended exit and bugged display
    - menu item: add option to show a default value (function ptr)
2024-02-23 Fix chairAdjust, disable reset-pin display - tested
    Tested chairAdjust using encoder and display in menu-mode
    Note: 1 relay is always on during startup
    - Fix bugged output state due to same pin used for display reset
    - Fix never turns off due to wrong pin assignment
    - Config: use actual encoder pins (not breakout board)
2024-02-26 Rework direction-detection, ignore bad pulses, optimize
    - trigger on rising edge only
    - ignore too short pulses - possible noise (config option)
    - ignore invalid pulse orders
    - debug log count of ignored sequences
2024-02-27 Fix bat voltage: lookup table, currentSensors: Add snap to zero
    display.cpp:
    Optimize battery voltage measurement
    While calibrating noticed it is very non-linear
    - outsource function to scale using lookup table
    - add lookup table to batvoltage measurement
    inserted many values to lookup table while testing
2024-02-29 Adjust button commands (dont toggle modes)
    Adjust button actions to match the current README
2024-03-03 WiFi on in HTTP-mode only, Add batt-threshold to timeout
    As initially planned starting wifi only when needed, at change to HTTP mode.
    Tested this on breakout board: ESP32 is not getting hot anymore!
    Also optimized timeout: only notify "forgot to turn off" when battery is below certain
    threshold (e.g. disable when charger is connected over night)
    main:
    - dont start wifi at startup anymore
2024-03-18 Fix unexpected movement in MASSAGE mode
    Revert change where massage commands were only generated at
    joystick change, since it has to be handled
    frequently in any case for motors to actually stop after certain time.
    Not tested yet
2024-05-20 Add menu item to set brake-deceleration
    Also simplify motorctl by removing two variables
    and using config struct instead
2024-05-30 Fix MASSAGE-mode messing up acceleration config
    - do not update nvs with low accel when changing to massage
    - store and restore previous value when changing from/to massage mode
2024-08-31 Add support for non-idle default mode, Set startup mode ADJUST
2024-09-04 Fix position tracking, stick mode - test success
2024-09-05 Minor fixes + optimizations - test success
2024-09-07 pcb: Add kicad project chairAdjust-relayBoard (pre-milling)
2024-09-08 pcb: add 3d-model, exports
2025-04-26 Create kicad project for speed-sensor-board
2025-08-24 extenderBoard: Add gyro board, Optimize i2c-boost + filter, Update footprints
2025-08-30 extenderBoard: Route I2C 12V boosting
2025-09-04 extenderBoard: Add ferrite-beads, Swap 12V TVS diodes
